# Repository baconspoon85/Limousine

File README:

Limousine is a drop in PCB replacement for Keychron Q9. This layout is intended to support a 30% layout plus right-side numpad.
-Hotswap MX switch sockets
-2u or split backspace
-Right side numpad with 2u or split 0.
-Traditional row stagger or alpha stagger layout options
-Multiple bottom row layout options including 7u, 10u (with 7u stabilizer mounts), 6u, split 2.25u/2.75u, and a solder only split 3u option
-Two EC11 push button encoders positions, both iterchangeable with hotswap MX switches
NOTE: The split 3u spacebar option is included to accomodate layouts with dedicated left hand mods. It requires soldered switches for the spacebar positions and removal of the hotswap socket for the 2.75u right spacebar position.

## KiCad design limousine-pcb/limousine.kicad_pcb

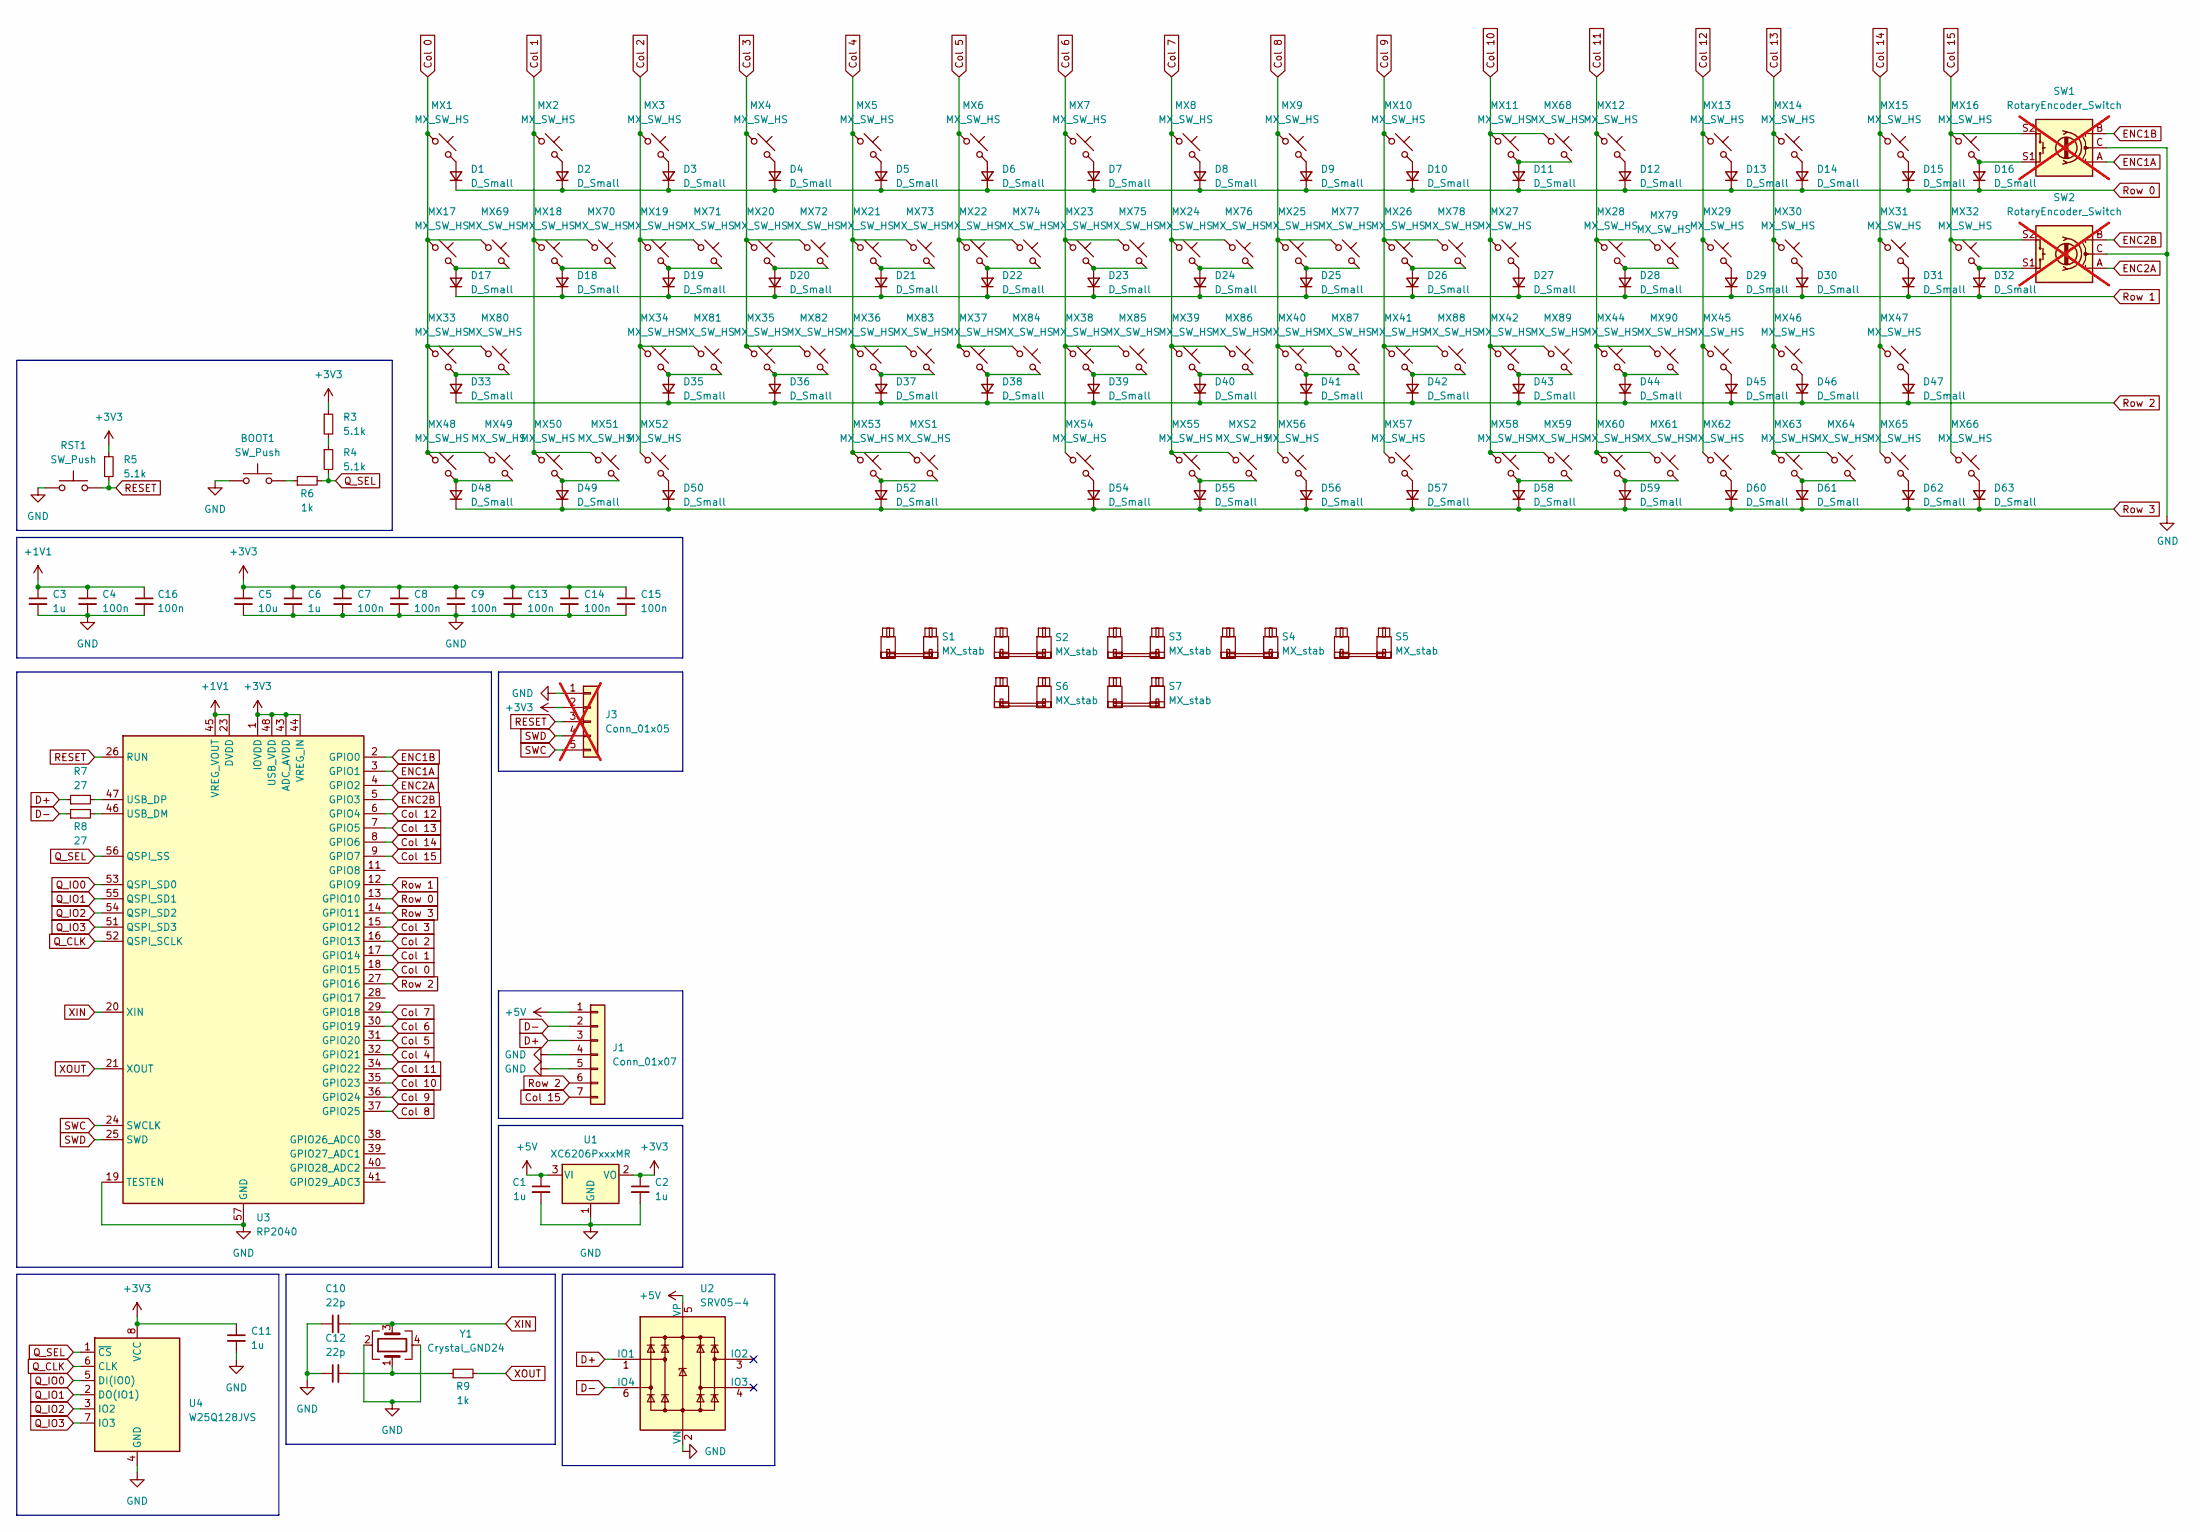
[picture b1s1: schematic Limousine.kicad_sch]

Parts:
BOOT1: SW_Push; SW_SPST_TL3342
C1, C2, C3, C6, C11: 1u; C_0402_1005Metric
C4, C7, C8, C9, C13, C14, C15, C16: 100n; C_0402_1005Metric
C5: 10u; C_0603_1608Metric
C10, C12: 22p; C_0402_1005Metric
D1, D2, D3, D4, D5, D6, D7, D8, D9, D10, D11, D12, D13, D14, D15, D16, D17, D18, D19, D20, D21, D22, D23, D24, D25, D26, D27, D28, D29, D30, D31, D32, D33, D35, D36, D37, D38, D39, D40, D41, D42, D43, D44, D45, D46, D47, D48, D49, D50, D52, D54, D55, D56, D57, D58, D59, D60, D61, D62, D63: D_Small; D_SOD-123_xomm
J1: Conn_01x07; JST_SH_BM07B-SRSS-TB_1x07-1MP_P1.00mm_Vertical
J3: Conn_01x05; PinHeader_1x05_P2.54mm_Vertical; not fitted
MX1, MX2, MX3, MX16, MX32: MX_SW_HS; SW_MX_HS_S_CPG151101S11_1u
MX4, MX5, MX6, MX7, MX8, MX9, MX10, MX11, MX12, MX13, MX14, MX15, MX17, MX18, MX19, MX20, MX21, MX22, MX23, MX24, MX25, MX26, MX27, MX28, MX29, MX30, MX31, MX34, MX35, MX36, MX37, MX38, MX39, MX40, MX41, MX42, MX45, MX46, MX47, MX48, MX50, MX52, MX53, MX54, MX55, MX56, MX57, MX59, MX61, MX62, MX63, MX64, MX65, MX66, MX68, MX70, MX71, MX72, MX73, MX74, MX75, MX76, MX77, MX78, MX81, MX82, MX83, MX84, MX85, MX86, MX87, MX88, MX89: MX_SW_HS; SW_MX_HS_CPG151101S11_1u
MX33, MX44: MX_SW_HS; SW_MX_HS_CPG151101S11_1.5u
MX49, MX51, MX58, MX60, MX69, MX90: MX_SW_HS; SW_MX_HS_CPG151101S11_1.25u
MX79, MX80: MX_SW_HS; SW_MX_HS_CPG151101S11_1.75u
MXS1, MXS2: MX_SW_HS; SW_MX_1u
R3, R4, R5: 5.1k; R_0402_1005Metric
R6, R9: 1k; R_0402_1005Metric
R7, R8: 27; R_0402_1005Metric
RST1: SW_Push; SW_SPST_TL3342
S1: MX_stab; STAB_MX_2.25u
S2: MX_stab; STAB_MX_7u
S3: MX_stab; STAB_MX_2.75u
S4, S5: MX_stab; STAB_MX_2u
S6, S7: MX_stab; STAB_MX_3u
SW1, SW2: RotaryEncoder_Switch; ROT_Alps_EC11E-Switch; not fitted
U1: XC6206PxxxMR; SOT-23-3
U2: SRV05-4; SOT-23-6-routable
U3: RP2040; QFN-56-1EP_7x7mm_P0.4mm_EP3.2x3.2mm
U4: W25Q128JVS; SOIC-8_5.23x5.23mm_P1.27mm
Y1: Crystal_GND24; Crystal_SMD_3225-4Pin_3.2x2.5mm

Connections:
+1V1: C3.1, C4.1, C16.1, U3.23 (DVDD), U3.45 (VREG_VOUT), U3.50 (DVDD)
+3V3: C2.1, C5.1, C6.1, C7.1, C8.1, C9.1, C11.1, C13.1, C14.1, C15.1, J3.2, R3.1, R5.1, U1.2 (VO), U3.1 (IOVDD), U3.10 (IOVDD), U3.22 (IOVDD), U3.33 (IOVDD), U3.42 (IOVDD), U3.43 (ADC_AVDD), U3.44 (VREG_IN), U3.48 (USB_VDD), U3.49 (IOVDD), U4.8 (VCC)
+5V: C1.1, J1.1, U1.3 (VI), U2.5 (VP)
Col 0: MX1.1, MX17.1, MX33.1, MX48.1, MX49.1, MX69.1, MX80.1, U3.18 (GPIO15)
Col 1: MX2.1, MX18.1, MX50.1, MX51.1, MX70.1, U3.17 (GPIO14)
Col 2: MX3.1, MX19.1, MX34.1, MX52.1, MX71.1, MX81.1, U3.16 (GPIO13)
Col 3: MX4.1, MX20.1, MX35.1, MX72.1, MX82.1, U3.15 (GPIO12)
Col 4: MX5.1, MX21.1, MX36.1, MX53.1, MX73.1, MX83.1, MXS1.1, U3.32 (GPIO21)
Col 5: MX6.1, MX22.1, MX37.1, MX74.1, MX84.1, U3.31 (GPIO20)
Col 6: MX7.1, MX23.1, MX38.1, MX54.1, MX75.1, MX85.1, U3.30 (GPIO19)
Col 7: MX8.1, MX24.1, MX39.1, MX55.1, MX76.1, MX86.1, MXS2.1, U3.29 (GPIO18)
Col 8: MX9.1, MX25.1, MX40.1, MX56.1, MX77.1, MX87.1, U3.37 (GPIO25)
Col 9: MX10.1, MX26.1, MX41.1, MX57.1, MX78.1, MX88.1, U3.36 (GPIO24)
Col 10: MX11.1, MX27.1, MX42.1, MX58.1, MX59.1, MX68.1, MX89.1, U3.35 (GPIO23)
Col 11: MX12.1, MX28.1, MX44.1, MX60.1, MX61.1, MX79.1, MX90.1, U3.34 (GPIO22)
Col 12: MX13.1, MX29.1, MX45.1, MX62.1, U3.6 (GPIO4)
Col 13: MX14.1, MX30.1, MX46.1, MX63.1, MX64.1, U3.7 (GPIO5)
Col 14: MX15.1, MX31.1, MX47.1, MX65.1, U3.8 (GPIO6)
Col 15: J1.7, MX16.1, MX32.1, MX66.1, SW1.S2, SW2.S2, U3.9 (GPIO7)
D+: J1.3, R7.1, U2.1 (IO1)
D-: J1.2, R8.1, U2.6 (IO4)
ENC1A: SW1.A, U3.3 (GPIO1)
ENC1B: SW1.B, U3.2 (GPIO0)
ENC2A: SW2.A, U3.4 (GPIO2)
ENC2B: SW2.B, U3.5 (GPIO3)
GND: BOOT1.1, C1.2, C2.2, C3.2, C4.2, C5.2, C6.2, C7.2, C8.2, C9.2, C10.1, C11.2, C12.1, C13.2, C14.2, C15.2, C16.2, J1.4, J1.5, J3.1, RST1.1, SW1.C, SW2.C, U1.1 (GND), U2.2 (VN), U3.19 (TESTEN), U3.57 (GND), U4.4 (GND), Y1.2, Y1.4
unnamed: BOOT1.2, R6.1
unnamed: C12.2, R9.1, Y1.1
unnamed: D1.2 (A), MX1.2
unnamed: D2.2 (A), MX2.2
unnamed: D3.2 (A), MX3.2
unnamed: D4.2 (A), MX4.2
unnamed: D5.2 (A), MX5.2
unnamed: D6.2 (A), MX6.2
unnamed: D7.2 (A), MX7.2
unnamed: D8.2 (A), MX8.2
unnamed: D9.2 (A), MX9.2
unnamed: D10.2 (A), MX10.2
unnamed: D11.2 (A), MX11.2, MX68.2
unnamed: D12.2 (A), MX12.2
unnamed: D13.2 (A), MX13.2
unnamed: D14.2 (A), MX14.2
unnamed: D15.2 (A), MX15.2
unnamed: D16.2 (A), MX16.2, SW1.S1
unnamed: D17.2 (A), MX17.2, MX69.2
unnamed: D18.2 (A), MX18.2, MX70.2
unnamed: D19.2 (A), MX19.2, MX71.2
unnamed: D20.2 (A), MX20.2, MX72.2
unnamed: D21.2 (A), MX21.2, MX73.2
unnamed: D22.2 (A), MX22.2, MX74.2
unnamed: D23.2 (A), MX23.2, MX75.2
unnamed: D24.2 (A), MX24.2, MX76.2
unnamed: D25.2 (A), MX25.2, MX77.2
unnamed: D26.2 (A), MX26.2, MX78.2
unnamed: D27.2 (A), MX27.2
unnamed: D28.2 (A), MX28.2, MX79.2
unnamed: D29.2 (A), MX29.2
unnamed: D30.2 (A), MX30.2
unnamed: D31.2 (A), MX31.2
unnamed: D32.2 (A), MX32.2, SW2.S1
unnamed: D33.2 (A), MX33.2, MX80.2
unnamed: D35.2 (A), MX34.2, MX81.2
unnamed: D36.2 (A), MX35.2, MX82.2
unnamed: D37.2 (A), MX36.2, MX83.2
unnamed: D38.2 (A), MX37.2, MX84.2
unnamed: D39.2 (A), MX38.2, MX85.2
unnamed: D40.2 (A), MX39.2, MX86.2
unnamed: D41.2 (A), MX40.2, MX87.2
unnamed: D42.2 (A), MX41.2, MX88.2
unnamed: D43.2 (A), MX42.2, MX89.2
unnamed: D44.2 (A), MX44.2, MX90.2
unnamed: D45.2 (A), MX45.2
unnamed: D46.2 (A), MX46.2
unnamed: D47.2 (A), MX47.2
unnamed: D48.2 (A), MX48.2, MX49.2
unnamed: D49.2 (A), MX50.2, MX51.2
unnamed: D50.2 (A), MX52.2
unnamed: D52.2 (A), MX53.2, MXS1.2
unnamed: D54.2 (A), MX54.2
unnamed: D55.2 (A), MX55.2, MXS2.2
unnamed: D56.2 (A), MX56.2
unnamed: D57.2 (A), MX57.2
unnamed: D58.2 (A), MX58.2, MX59.2
unnamed: D59.2 (A), MX60.2, MX61.2
unnamed: D60.2 (A), MX62.2
unnamed: D61.2 (A), MX63.2, MX64.2
unnamed: D62.2 (A), MX65.2
unnamed: D63.2 (A), MX66.2
unnamed: R3.2, R4.1
unnamed: R8.2, U3.46 (USB_DM)
unnamed: R7.2, U3.47 (USB_DP)
Q_CLK: U3.52 (QSPI_SCLK), U4.6 (CLK)
Q_IO0: U3.53 (QSPI_SD0), U4.5 (DI(IO0))
Q_IO1: U3.55 (QSPI_SD1), U4.2 (DO(IO1))
Q_IO2: U3.54 (QSPI_SD2), U4.3 (IO2)
Q_IO3: U3.51 (QSPI_SD3), U4.7 (IO3)
Q_SEL: R4.2, R6.2, U3.56 (QSPI_SS), U4.1 (~CS)
RESET: J3.3, R5.2, RST1.2, U3.26 (RUN)
Row 0: D1.1 (K), D2.1 (K), D3.1 (K), D4.1 (K), D5.1 (K), D6.1 (K), D7.1 (K), D8.1 (K), D9.1 (K), D10.1 (K), D11.1 (K), D12.1 (K), D13.1 (K), D14.1 (K), D15.1 (K), D16.1 (K), U3.13 (GPIO10)
Row 1: D17.1 (K), D18.1 (K), D19.1 (K), D20.1 (K), D21.1 (K), D22.1 (K), D23.1 (K), D24.1 (K), D25.1 (K), D26.1 (K), D27.1 (K), D28.1 (K), D29.1 (K), D30.1 (K), D31.1 (K), D32.1 (K), U3.12 (GPIO9)
Row 2: D33.1 (K), D35.1 (K), D36.1 (K), D37.1 (K), D38.1 (K), D39.1 (K), D40.1 (K), D41.1 (K), D42.1 (K), D43.1 (K), D44.1 (K), D45.1 (K), D46.1 (K), D47.1 (K), J1.6, U3.27 (GPIO16)
Row 3: D48.1 (K), D49.1 (K), D50.1 (K), D52.1 (K), D54.1 (K), D55.1 (K), D56.1 (K), D57.1 (K), D58.1 (K), D59.1 (K), D60.1 (K), D61.1 (K), D62.1 (K), D63.1 (K), U3.14 (GPIO11)
SWC: J3.5, U3.24 (SWCLK)
SWD: J3.4, U3.25 (SWD)
XIN: C10.2, U3.20 (XIN), Y1.3
XOUT: R9.2, U3.21 (XOUT)

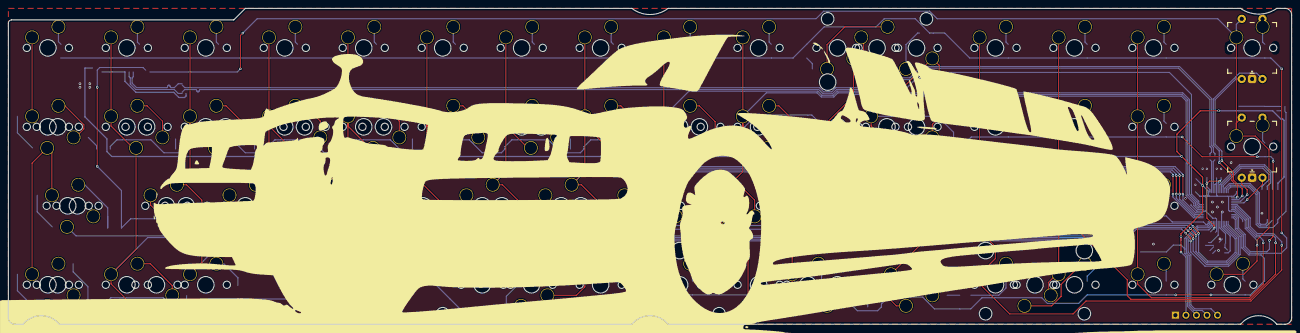
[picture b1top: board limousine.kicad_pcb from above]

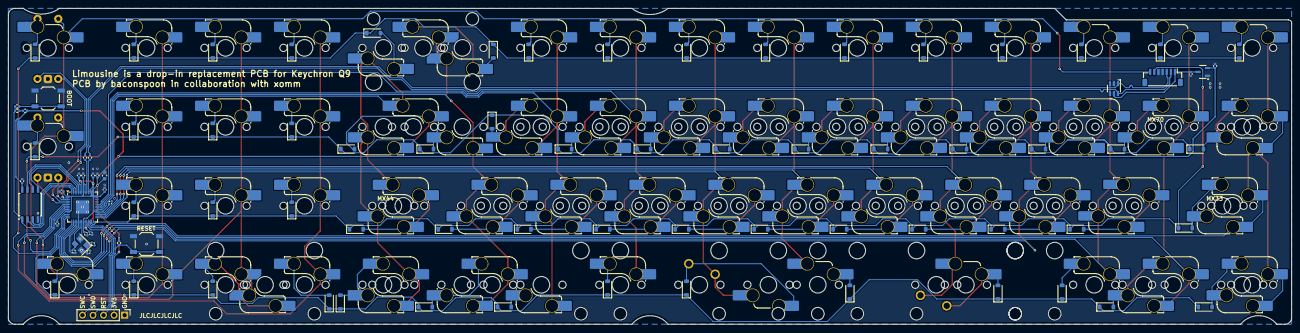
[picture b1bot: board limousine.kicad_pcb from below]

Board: 2 copper layers, 309.6 x 76.2 mm, 191 parts (180 on the bottom side), 106 nets.

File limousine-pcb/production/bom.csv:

Designator,Footprint,Quantity,Value,LCSC Part #
"BOOT1, RST1",SW_SPST_TL3342,2,SW_Push,C318884
"C1, C11, C2, C3, C6",402,5,1u,C52923
"C10, C12",402,2,22p,C1555
"C13, C14, C15, C16, C4, C7, C8, C9",402,8,100n,C1525
C5,603,1,10u,C19702
"D1, D10, D11, D12, D13, D14, D15, D16, D17, D18, D19, D2, D20, D21, D22, D23, D24, D25, D26, D27, D28, D29, D3, D30, D31, D32, D33, D35, D36, D37, D38, D39, D4, D40, D41, D42, D43, D44, D45, D46, D47, D48, D49, D5, D50, D52, D54, D55, D56, D57, D58, D59, D6, D60, D61, D62, D63, D7, D8, D9",D_SOD-123_xomm,60,D_Small,C81598
J1,JST_SH_BM07B-SRSS-TB_1x07-1MP_P1.00mm_Vertical,1,Conn_01x07,C160393
"MX1, MX16, MX2, MX3, MX32, MX53, MX54, MX55",SW_MX_HS_S_CPG151101S11_1u,8,MX_SW_HS,C5156480
"MX10, MX11, MX12, MX13, MX14, MX15, MX17, MX18, MX19, MX20, MX21, MX22, MX23, MX24, MX25, MX26, MX27, MX28, MX29, MX30, MX31, MX34, MX35, MX36, MX37, MX38, MX39, MX4, MX40, MX41, MX42, MX45, MX46, MX47, MX48, MX5, MX50, MX52, MX56, MX57, MX59, MX6, MX61, MX62, MX63, MX64, MX65, MX66, MX68, MX7, MX70, MX71, MX72, MX73, MX74, MX75, MX76, MX77, MX78, MX8, MX81, MX82, MX83, MX84, MX85, MX86, MX87, MX88, MX89, MX9",SW_MX_HS_CPG151101S11_1u,70,MX_SW_HS,C5156480
"MX33, MX44",SW_MX_HS_CPG151101S11_1.5u,2,MX_SW_HS,C5156480
"MX49, MX51, MX58, MX60, MX69, MX90",SW_MX_HS_CPG151101S11_1.25u,6,MX_SW_HS,C5156480
"MX79, MX80",SW_MX_HS_CPG151101S11_1.75u,2,MX_SW_HS,C5156480
"MXS1, MXS2",SW_MX_1u,2,MX_SW_HS,C5156480
"R3, R4, R5",402,3,5.1k,C25905
"R6, R9",402,2,1k,C11702
"R7, R8",402,2,27,C25100
U1,SOT-23-3,1,XC6206PxxxMR,C2897477
U2,SOT-23-6-routable,1,SRV05-4,C2836319
U3,QFN-56-1EP_7x7mm_P0.4mm_EP3.2x3.2mm,1,RP2040,C2040
U4,SOIC-8_5.23x5.23mm_P1.27mm,1,W25Q128JVS,C97521
Y1,Crystal_SMD_3225-4Pin_3.2x2.5mm,1,Crystal_GND24,C403945

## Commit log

2024-09-17 add pcb render
2024-09-18 added plate files
2024-10-21 update production files used in v1 run
